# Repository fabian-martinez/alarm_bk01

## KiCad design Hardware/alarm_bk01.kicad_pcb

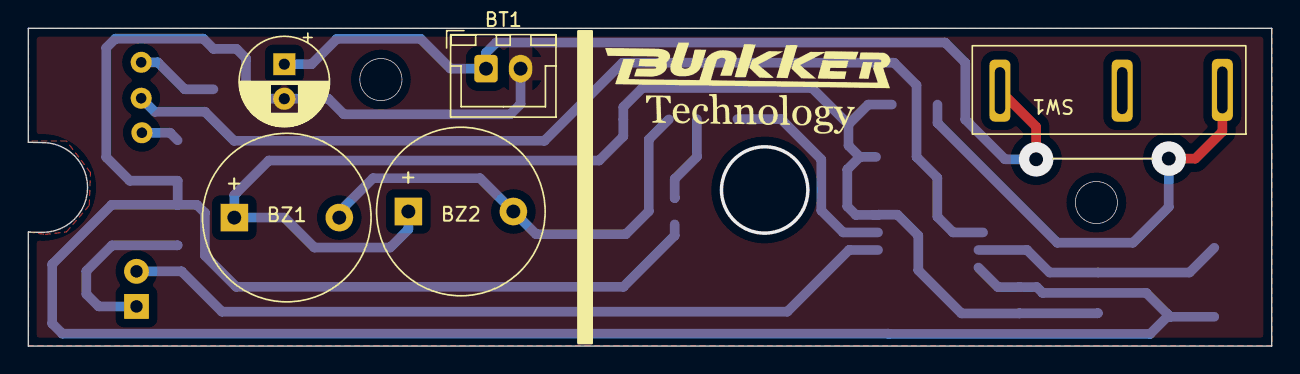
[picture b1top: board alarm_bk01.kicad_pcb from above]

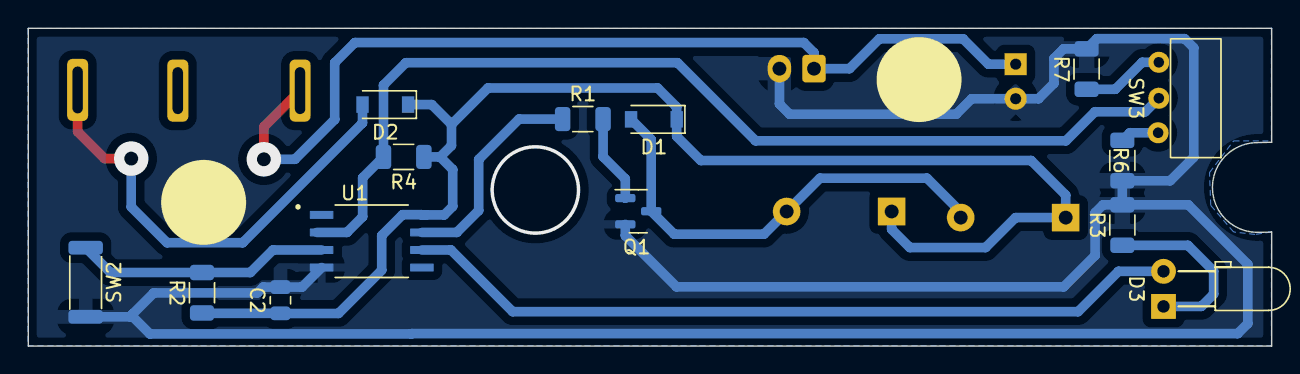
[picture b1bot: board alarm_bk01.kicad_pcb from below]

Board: 2 copper layers, 90.0 x 23.0 mm, 19 parts (14 on the bottom side), 13 nets.

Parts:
BT1: Battery; JST_XH_B2B-XH-A_1x02_P2.50mm_Vertical
BZ1, BZ2: Buzzer; Buzzer_12x9.5RM7.6
C1: 100u; CP_Radial_D6.3mm_P2.50mm
C2: 47uF; C_0805_2012Metric
D1, D2: 1N4148; D_SOD-123
D3: LED; LED_D3.0mm_Horizontal_O3.81mm_Z2.0mm
Q1: MMBT3904; SOT-23
R1: 180; R_1206_3216Metric
R2: 10k; R_1206_3216Metric
R3: 6.8K; R_1206_3216Metric
R4: 100K; R_1206_3216Metric
R6: LOW; R_1206_3216Metric
R7: HIGH; R_1206_3216Metric
SW1: START; microswitch
SW2: Sensor; CX-2548
SW3: SW_SPDT; SW-horizontal
U1: ATtiny85; SOIC127P798X216-8N

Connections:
0: BT1.2 (-), C1.2, C2.2, Q1.2 (E), R3.2, R6.2, R7.2, SW2.1, U1.4 (GND)
/ON_NET: D2.2 (A), SW1.NC
/POWER: BT1.1 (+), C1.1, SW1.COM
Indicator: D3.2 (A), U1.6 (PB1)
unnamed: BZ1.2 (+), BZ2.2 (+), D1.2 (A), Q1.3 (C)
unnamed: D3.1 (K), R3.1
unnamed: Q1.1 (B), R1.2
unnamed: R6.1, SW3.3 (C)
unnamed: R7.1, SW3.1 (A)
VCC: BZ1.1 (-), BZ2.1 (-), C2.1, D1.1 (K), D2.1 (K), R2.1, R4.1, U1.8 (VCC)
alarma: R1.1, U1.7 (PB2)
sensibilidad: R4.2, SW3.2 (B), U1.2 (XTAL1/PB3)
sensor: R2.2, SW2.2, U1.3 (XTAL2/PB4)

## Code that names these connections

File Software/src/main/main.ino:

#include <avr/io.h>
#include <avr/interrupt.h>

#define INT_PIN PB4           
#define PCINT_VECTOR PCINT0_vect      // This step is not necessary - it's a naming thing for clarit

// Out Pins
#define ALARM_PIN PB2
#define INDICATOR_PIN PB1

// In Pins
#define SENSIBILTY_PIN PB3

int IDLE_TIME = 4; //two minutes to restart counter if the alar is not enable //Duration of alarm 36.000 milliseconds

int sensibilityValue;
unsigned int vibrationsCounter = 0;  // counter for the number vibrations
unsigned int vibrationsBefore = 0;  // counter for the number vibrations
unsigned long startIdleTime = 0; //Get current time to reset
bool alarm = false;

void setup() {

  delay(500);

  // put your setup code here, to run once:
  pinMode(ALARM_PIN, OUTPUT);
  pinMode(INDICATOR_PIN, OUTPUT);
  pinMode(SENSIBILTY_PIN, INPUT);

  vibrationsCounter = 0;
  vibrationsBefore = 0;
  startIdleTime = 0;

  delay(10000);

  tones(100);
  
  cli();                            // Disable interrupts during setup
  
  sensibilityValue = analogRead(SENSIBILTY_PIN)*100; /// 4500 y 2200
  alarm = false;

  PCMSK |= (1 << INT_PIN);          // Enable interrupt handler (ISR) for our chosen interrupt pin (PCINT1/PB1/pin 6)
  GIMSK |= (1 << PCIE);             // Enable PCINT interrupt in the general interrupt mask
  pinMode(INT_PIN, INPUT_PULLUP);

  sei(); 
     // Set our interrupt pin as input with a pullup to keep it stable

}

void loop() {
  
  // if time beetwen vibration is more than IDLE_TIME restart counter.
  if (startIdleTime >= IDLE_TIME){
    startIdleTime = 0;
    vibrationsCounter = 0;
    alarm = false;
  } 

  if(vibrationsCounter >= sensibilityValue){
    alarm = true;
  }

  if( alarm ){
    tones(10);
    delay(5000);
    tones(50);
    delay(10000);
    startIdleTime++;
  }

  delay(100);

}

void tones(int counts){
  for(int count = 0; count < counts; count++){
    digitalWrite(ALARM_PIN, HIGH);
    digitalWrite(INDICATOR_PIN, HIGH);
    delay(50);
    digitalWrite(ALARM_PIN, LOW);
    digitalWrite(INDICATOR_PIN, LOW);
    delay(50);
    digitalWrite(ALARM_PIN, HIGH);
    digitalWrite(INDICATOR_PIN, HIGH);
    delay(200);
    digitalWrite(ALARM_PIN, LOW);
    digitalWrite(INDICATOR_PIN, LOW);
    delay(50);
  }
}

ISR(PCINT_VECTOR)
{
  vibrationsCounter++;
}

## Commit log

2023-03-23 add main project elements
2023-03-23 add smd design file
2023-03-23 update gitignore to autosave file
2023-03-23 reorganice components
2023-03-23 add second buzzer in schematic
2023-03-24 finish design
2023-03-24 update pcb model
2023-03-29 ignore holes files
2023-04-13 pcb and holes of the new model
2023-04-14 add components locked to pcb
2023-04-26 Finish smd board
2023-07-07 last update
2023-07-09 Add brand in pcb
